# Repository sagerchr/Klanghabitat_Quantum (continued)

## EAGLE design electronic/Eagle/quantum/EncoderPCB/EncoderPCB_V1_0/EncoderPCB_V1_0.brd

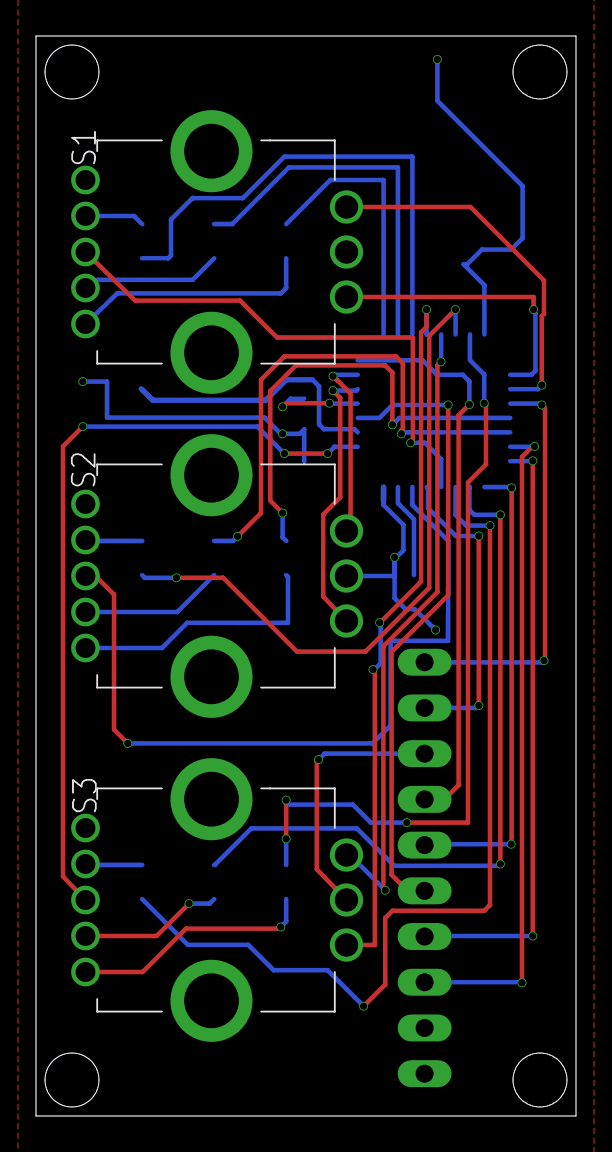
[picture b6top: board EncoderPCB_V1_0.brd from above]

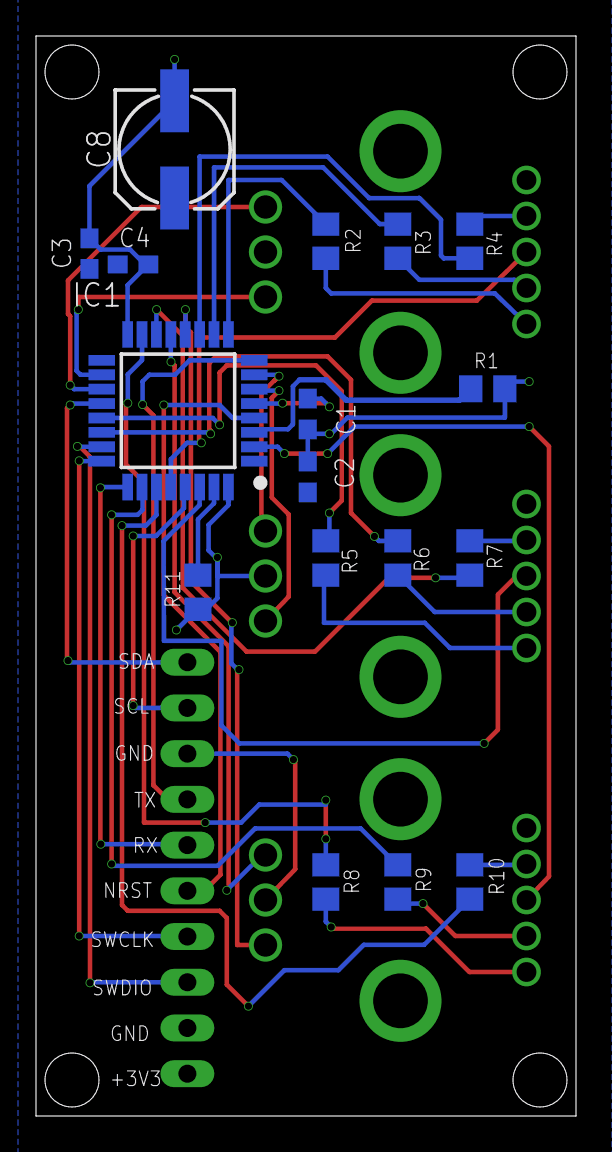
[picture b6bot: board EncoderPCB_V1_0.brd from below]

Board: 2 copper layers, 30.0 x 60.0 mm, 30 parts (17 on the bottom side), 38 nets.

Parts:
3V1: TPTHT; THT_PIN
C1, C2, C3, C4: 100nF; C0603
C8: 4,7µF; 153CLV-0605
GND, GND2: TPTHT; THT_PIN
I2C1_SCL, I2C1_SDA: TPTHT; THT_PIN
IC1: STM32F031K6T6; QFP80P900X900X160-32N
NRST: TPTHT; THT_PIN
R1, R11: 10k; R0805
R2, R3, R4, R5, R6, R7, R8, R9, R10: R0805
S1, S2, S3: PEL12T-4225S-S1024; PEL12T4225SS1024
SWCLK: TPTHT; THT_PIN
SWDIO: TPTHT; THT_PIN
USART1_RX1, USART1_TX: TPTHT; THT_PIN

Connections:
+3V3: 3V1.P$1, C1.1, C2.1, C3.1, C4.1, C8.+, IC1.1, IC1.5, IC1.17, S1.5, S2.5, S3.5
ADRR.: IC1.3, R1.2
BOOT_0: IC1.31, R11.2
BUTTON_ENC1: IC1.28, S1.3
BUTTON_ENC2: IC1.30, S2.3
BUTTON_ENC3: IC1.2, S3.3
B_ENC1: IC1.11, R4.1
B_ENC2: IC1.14, R7.1
B_ENC3: IC1.27, R10.1
ENCODER1_A: IC1.18, S1.A1
ENCODER1_B: IC1.19, S1.B1
ENCODER2_A: IC1.6, S2.A1
ENCODER2_B: IC1.7, S2.B1
ENCODER3_A: IC1.12, S3.A1
ENCODER3_B: IC1.13, S3.B1
GND: C1.2, C2.2, C3.2, C4.2, C8.-, GND.P$1, GND2.P$1, IC1.16, IC1.32, R1.1, R11.1, S1.C1, S2.C1, S3.C1
G_ENC1: IC1.10, R3.1
G_ENC2: IC1.22, R6.1
G_ENC3: IC1.26, R9.1
I2C1_SCL: I2C1_SCL.P$1, IC1.29
I2C1_SDA: I2C1_SDA.P$1, IC1.20
unnamed: R2.2, S1.1
unnamed: R3.2, S1.2
unnamed: R5.2, S2.1
unnamed: R4.2, S1.4
unnamed: R6.2, S2.2
unnamed: R7.2, S2.4
unnamed: R8.2, S3.1
unnamed: R9.2, S3.2
unnamed: R10.2, S3.4
NRST: IC1.4, NRST.P$1
R_ENC1: IC1.9, R2.1
R_ENC2: IC1.21, R5.1
R_ENC3: IC1.15, R8.1
SWCLK: IC1.24, SWCLK.P$1
SWDIO: IC1.23, SWDIO.P$1
USART1_RX1: IC1.25, USART1_RX1.P$1
USART1_TX: IC1.8, USART1_TX.P$1
